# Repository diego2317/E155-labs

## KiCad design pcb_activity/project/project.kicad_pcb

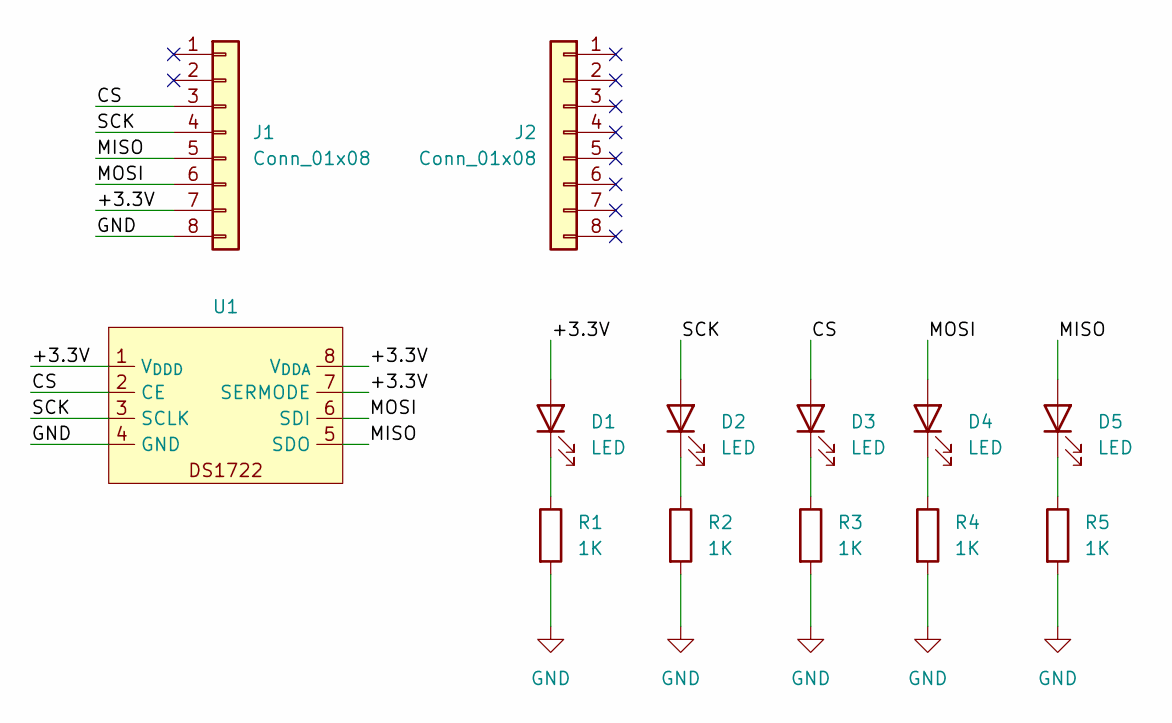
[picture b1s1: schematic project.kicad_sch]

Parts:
D1, D2, D3, D4, D5: LED; LED_0805_2012Metric
J1, J2: Conn_01x08; PinSocket_1x08_P2.54mm_Vertical
R1, R2, R3, R4, R5: 1K; R_0805_2012Metric
U1: PinSocket_1x08_P2.54mm_Vertical

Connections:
/+3.3V: D1.2 (A), J1.7, U1.1 (V_{DDD}), U1.7 (SERMODE), U1.8 (V_{DDA})
/CS: D3.2 (A), J1.3, U1.2 (CE)
/MISO: D5.2 (A), J1.5, U1.5 (SDO)
/MOSI: D4.2 (A), J1.6, U1.6 (SDI)
/SCK: D2.2 (A), J1.4, U1.3 (SCLK)
GND: J1.8, R1.2, R2.2, R3.2, R4.2, R5.2, U1.4 (GND)
unnamed: D1.1 (K), R1.1
unnamed: D2.1 (K), R2.1
unnamed: D3.1 (K), R3.1
unnamed: D4.1 (K), R4.1
unnamed: D5.1 (K), R5.1

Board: 2 copper layers, 12 parts (0 on the bottom side), 11 nets, no tracks yet.

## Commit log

2025-08-26 initializing E155 repo
2025-08-29 Reorganized stuff
2025-08-29 Setup the project. idk how I'm gonna do this
2025-08-30 Starting over
2025-08-30 Ok hopefully maybe fixed my setup
2025-08-30 It won't synthesize on my laptop. I'll try the lab computers?
2025-08-30 Design synthesizes now
2025-08-30 set pins. led[2] isn't blinking, need to figure that out using testbench probably
2025-09-01 Started writing testbench but I really neeed dinner. Also hopefully fixed blinky led?
2025-09-03 i hate sinulation
2025-09-03 updated testbench stuff
2025-09-03 it works now hooray
2025-09-03 fixed light up logic for 6
2025-09-03 Update display_controller_tb.sv
    comments
2025-09-03 created ai prototype project
2025-09-03 somethign
2025-09-03 Create .gitignore and folder setup
2025-09-03 closed ai prototype from lab 1 and it acted weird
2025-09-03 updated gitignore, made new files
2025-09-03 started writing verilog
2025-09-04 start combining into 1 module
2025-09-05 Edited design to meet requirements
2025-09-05 renamed transistor signal
2025-09-07 Something is broken with the testbench
2025-09-07 Realized i wasn't initializing some modules lol
2025-09-08 Got simulation working
2025-09-08 Changed rdf
2025-09-08 added test vectors
2025-09-08 Wrote top level testbench, tried new format
2025-09-08 hopefully fix
2025-09-08 copied code just in case
2025-09-09 board ledslighting up, display not turning on
2025-09-09 works now lol
2025-09-10 Changed display_controller to use a mux instead of a toggle flop
2025-09-10 boom bap everything works
2025-09-10 fixed reset
2025-09-10 added comments
2025-09-10 more comments
2025-09-10 ai prototype
2025-09-14 Started work. Wowza this is gonna be hard
2025-09-14 Yeah this is gonna be tough
2025-09-14 Ok hopefully this will work
2025-09-15 doesn't work at all. gues i do have to look at waveforms
2025-09-15 updated verilog
2025-09-15 chipping away
2025-09-16 It works
2025-09-16 fixing conflicts
2025-09-16 copying verilog to be safe
2025-09-16 deleting radiant project
2025-09-16 RAAAAA KEYPAD SCANNING AND VALUE ASSIGNMENT SHOULD WORK
2025-09-16 Got keypad scan sim to work
2025-09-16 Update transcript
2025-09-16 I have to redo pretty much everything because I encoded the rows backwards! Yay!
2025-09-17 Ok I think it's working partially?
2025-09-17 Changed logic back
2025-09-17 Finished (kinda)
    In theory all combinations of inputs should work now, unless you press two keys in the same row during debouncing. Gonna build it, see how it goes
2025-09-17 closed radiant
2025-09-17 RAAAAAAAAAAAAAAAAAAAAAAA
2025-09-17 renaming ports
2025-09-18 i gotta redo
2025-09-22 Hopefully this fixes the multiple keys on the same row
2025-09-23 Lab 3 AI prototype
2025-09-23 row multipress works but columns doesn't now
2025-09-23 idfk
2025-09-30 Setup
2025-10-01 Finished writing libraries
2025-10-04 My board won't program?
2025-10-05 idk what's going on
2025-10-06 did stuff
2025-10-07 comments, added hot cross buns
2025-10-07 comments
2025-10-08 Finished
2025-10-08 wrote a bunch of code
2025-10-08 moved stuff out of main
2025-10-08 lowkey done
2025-10-09 fixed rps calculation. added systick handler
2025-10-16 finished writing libs
2025-10-16 Finished (if everything works first try)
2025-10-20 work
2025-10-22 poked around and maybe found a mistake or two?
2025-10-22 lab 7 setup
2025-10-23 actually finsihed
2025-10-23 done
2025-11-04 still not working, gonna change some logic
2025-11-05 same row still doesnt work
2025-11-05 best version, still not excellent
2025-11-05 DONE RAAAAAAAAAA
